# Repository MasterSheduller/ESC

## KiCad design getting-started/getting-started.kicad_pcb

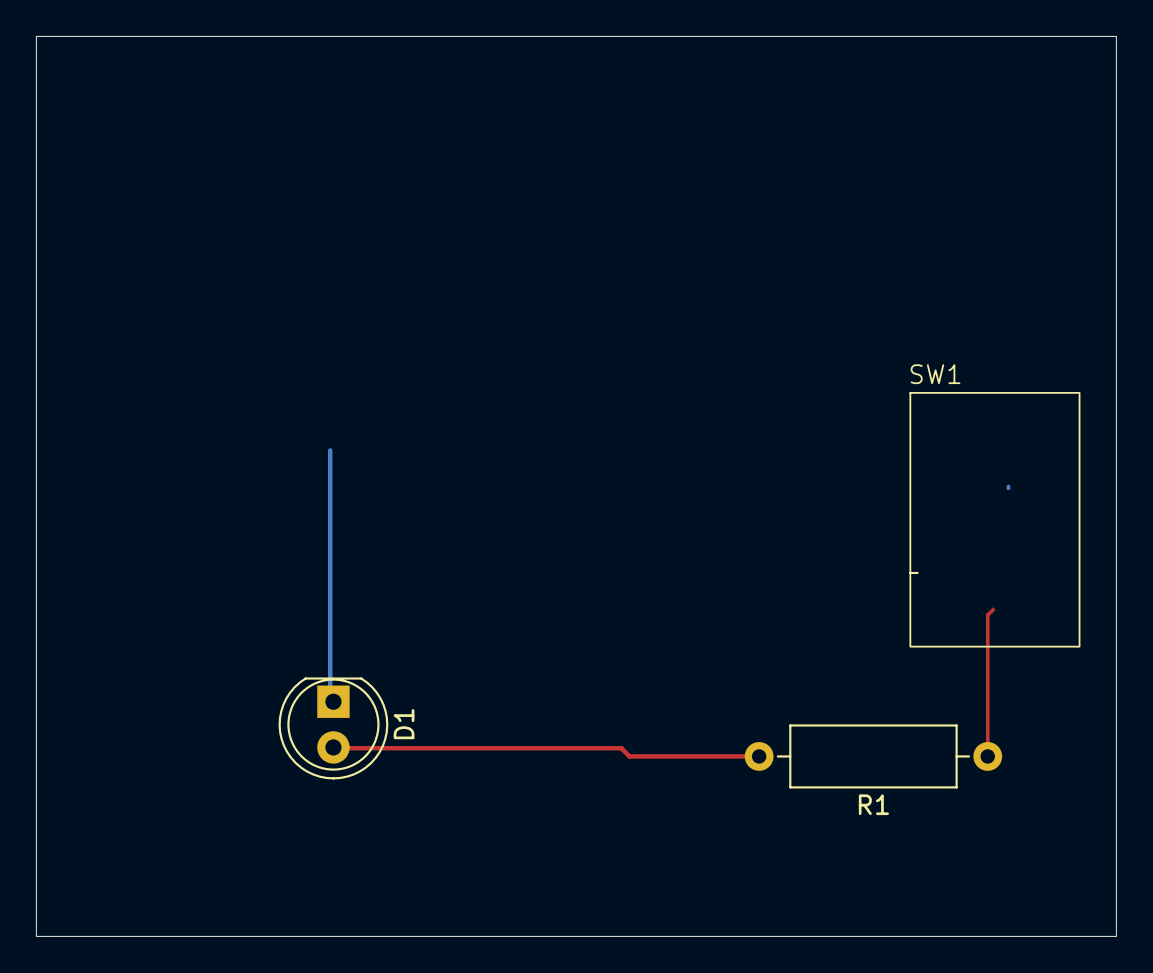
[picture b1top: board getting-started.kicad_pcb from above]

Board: 2 copper layers, 60.0 x 50.0 mm, 4 parts (1 on the bottom side), 3 nets.

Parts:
BT1: 3V; BatteryHolder_Keystone_1058_1x2032
D1: red; LED_D5.0mm
R1: 1k; R_Axial_DIN0309_L9.0mm_D3.2mm_P12.70mm_Horizontal
SW1: M2011S3A1W03; getting-started.pretty

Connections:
/led: D1.2 (A), R1.2
unnamed: BT1.1 (+), BT1.2 (-), D1.1 (K), SW1.2 (A)
VCC: R1.1, SW1.3 (B)

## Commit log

2025-05-02 Add FLTK demo project
